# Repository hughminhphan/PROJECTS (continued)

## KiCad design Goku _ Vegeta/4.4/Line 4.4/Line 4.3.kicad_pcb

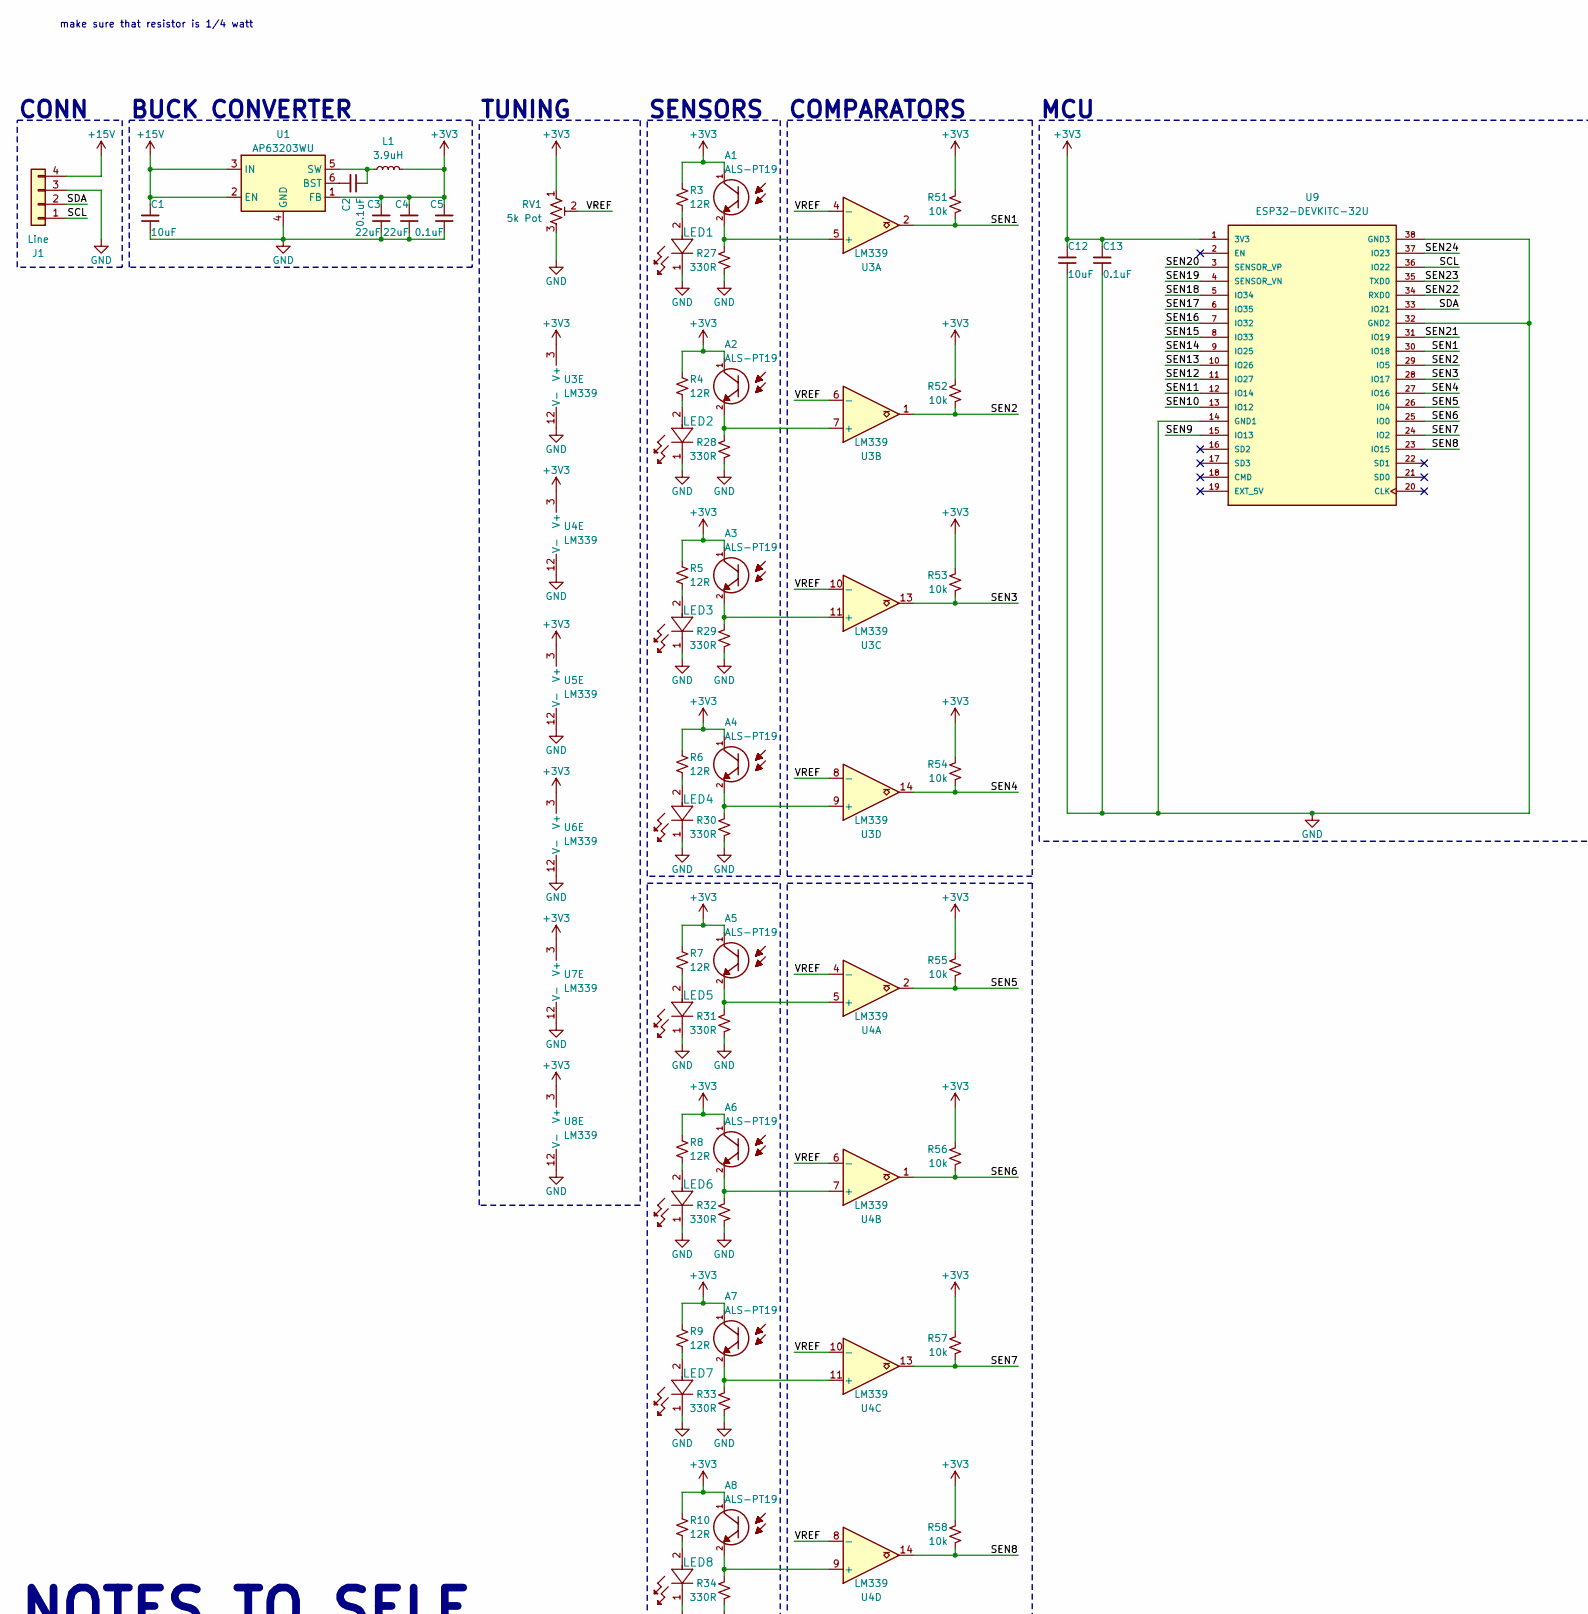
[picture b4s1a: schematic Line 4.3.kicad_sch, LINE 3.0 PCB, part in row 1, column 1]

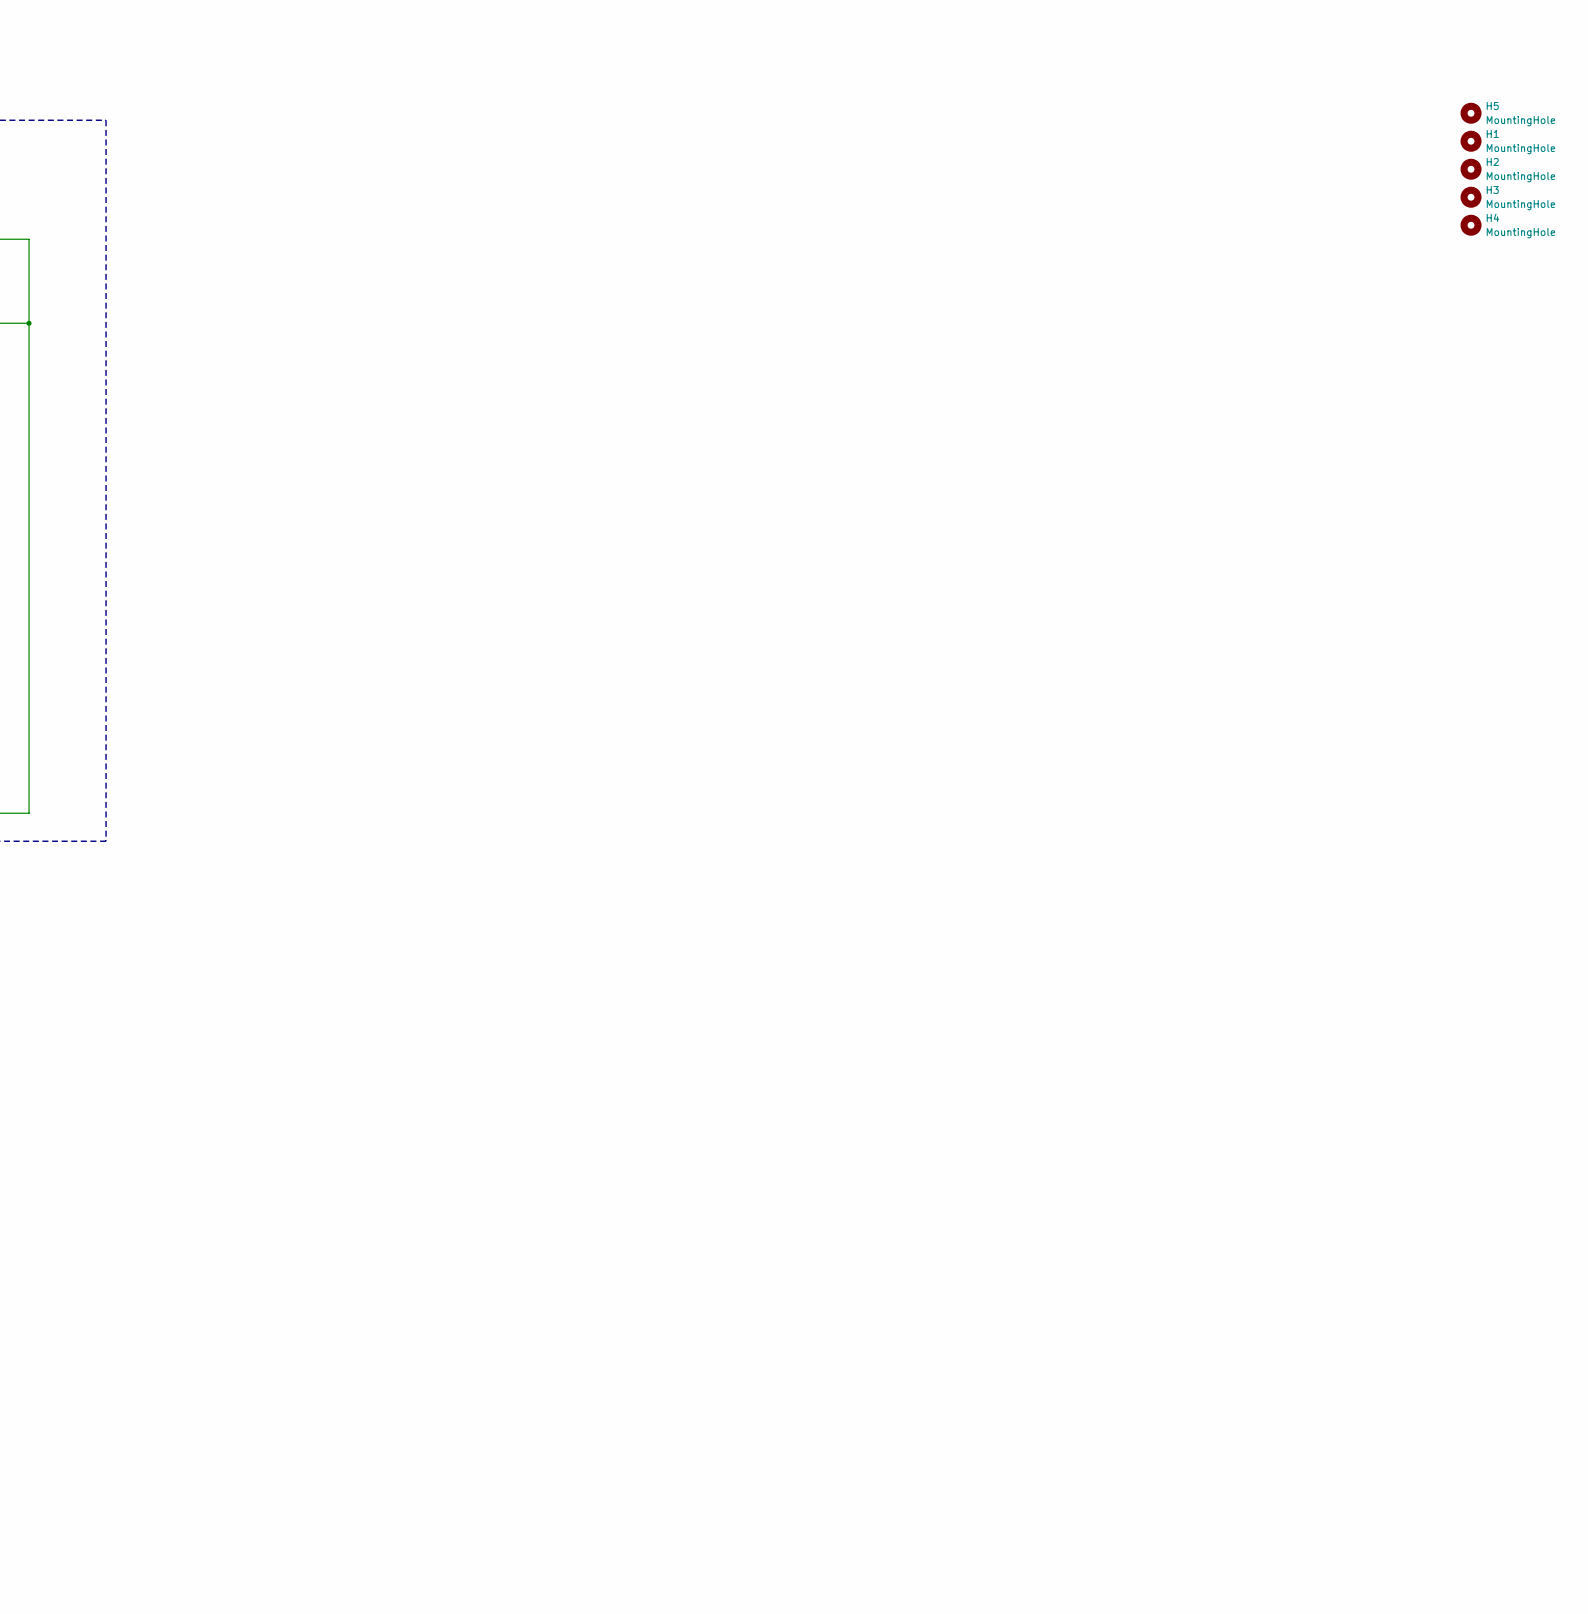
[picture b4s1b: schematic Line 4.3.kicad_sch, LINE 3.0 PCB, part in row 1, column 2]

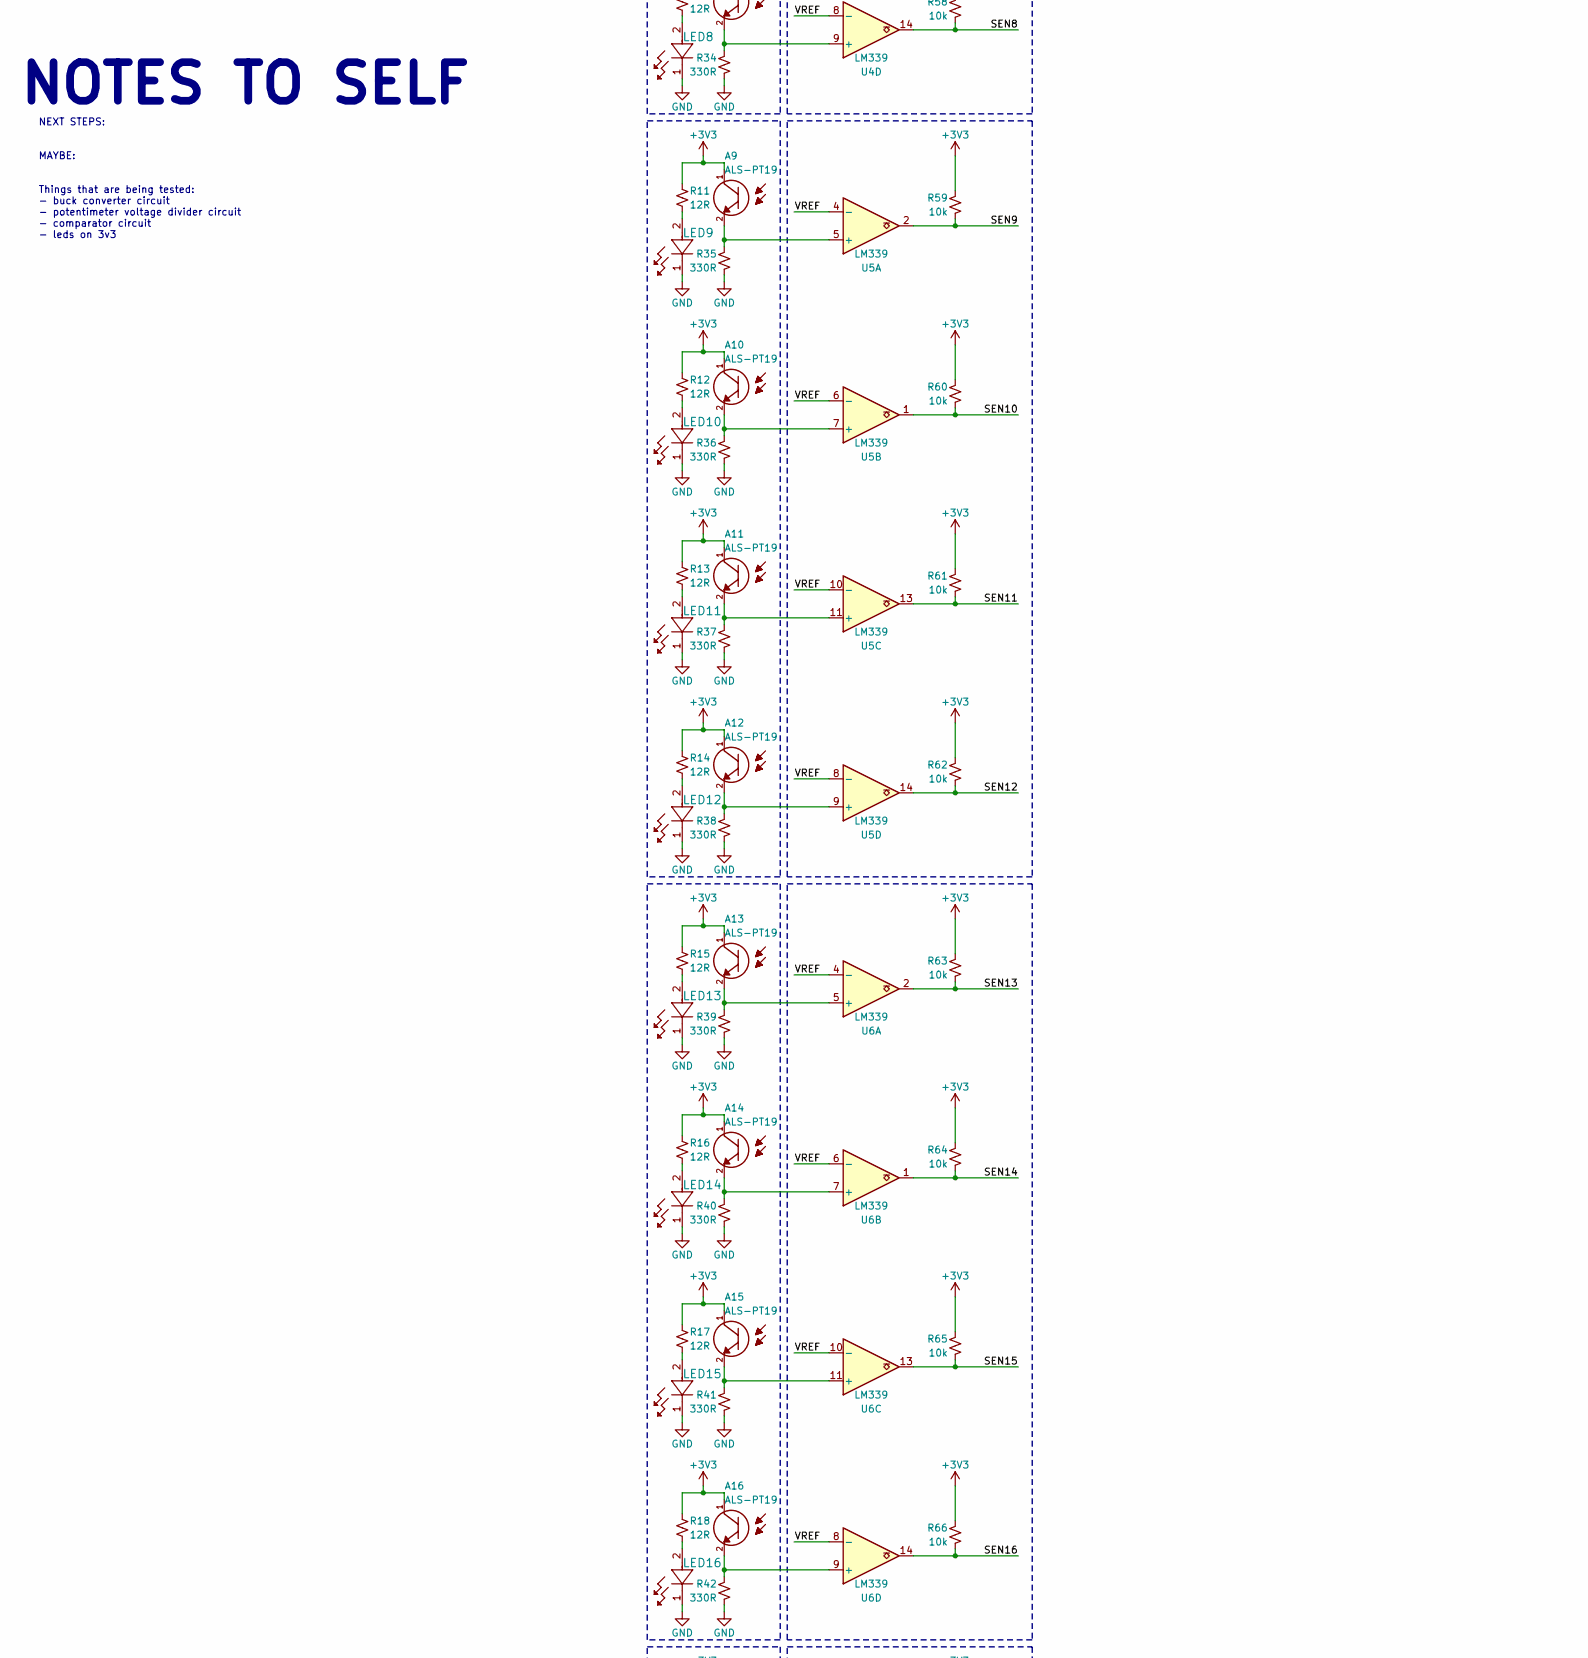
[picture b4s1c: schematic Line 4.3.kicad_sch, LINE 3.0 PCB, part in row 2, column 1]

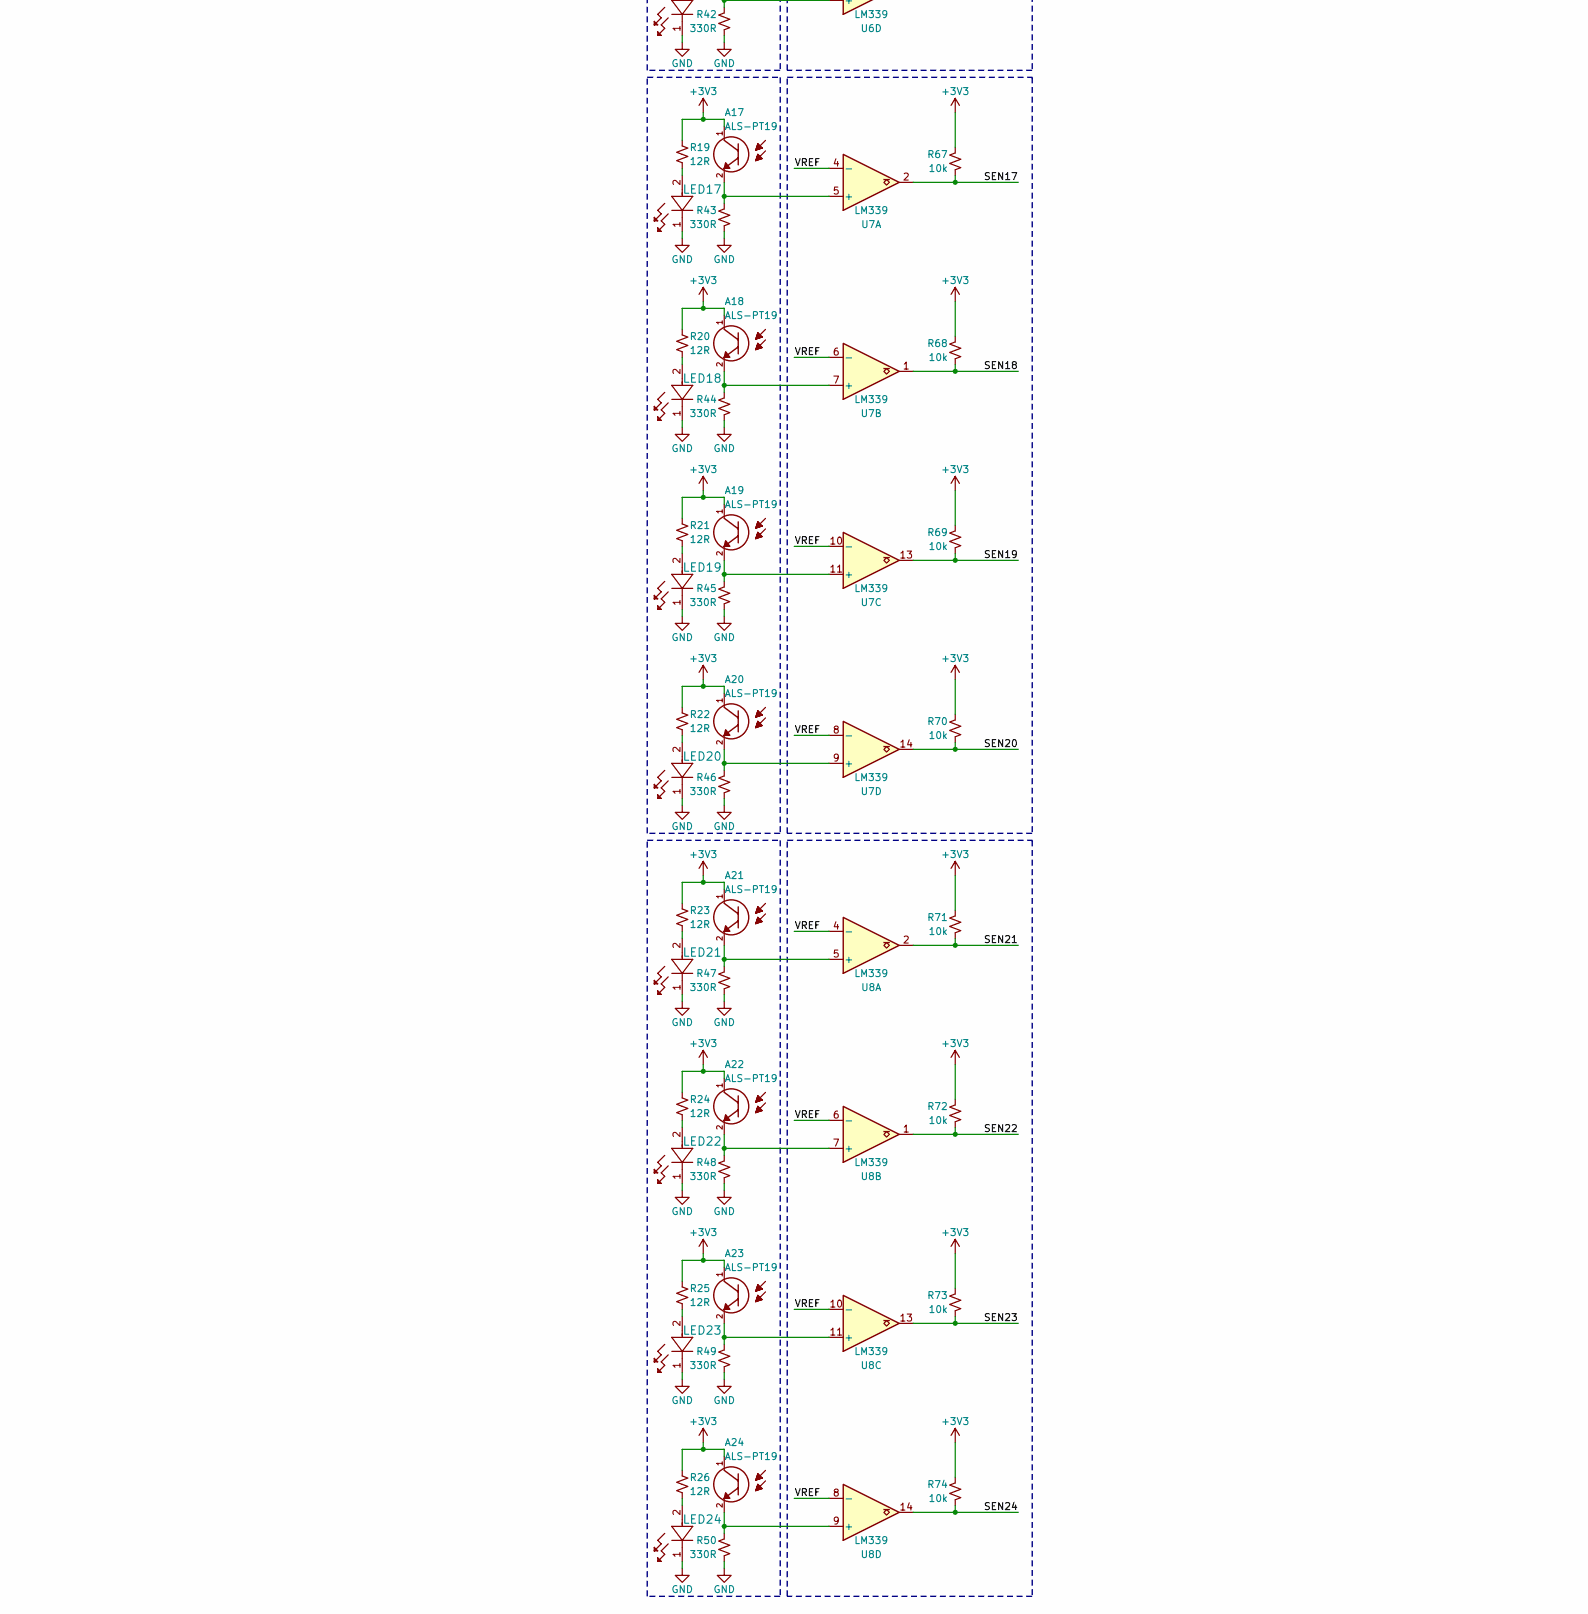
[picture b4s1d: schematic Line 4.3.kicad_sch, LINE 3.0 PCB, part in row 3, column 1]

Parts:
A1, A2, A3, A4, A5, A6, A7, A8, A9, A10, A11, A12, A13, A14, A15, A16, A17, A18, A19, A20, A21, A22, A23, A24: ALS-PT19; XDCR_ALS-PT19-315C_L177_TR8; PARTREV 5
C1, C12: 10uF; C_0805_2012Metric
C2, C5, C13: 0.1uF; C_0805_2012Metric
C3, C4: 22uF; C_0805_2012Metric
H1, H5: MountingHole; MountingHole_2.2mm_M2
H2, H3, H4: MountingHole; MountingHole_3.2mm_M3
J1: Line; JST_XH_B4B-XH-A_1x04_P2.50mm_Vertical
L1: 3.9uH; L_Bourns-SRU8043
LED1, LED2, LED3, LED4, LED5, LED6, LED7, LED8, LED9, LED10, LED11, LED12, LED13, LED14, LED15, LED16, LED17, LED18, LED19, LED20, LED21, LED22, LED23, LED24: JB2835AWT-W-U30GA0000-N0000001; LED_J2835_CRW
R3, R4, R5, R6, R7, R8, R9, R10, R11, R12, R13, R14, R15, R16, R17, R18, R19, R20, R21, R22, R23, R24, R25, R26: 12R; R_0805_2012Metric
R27, R28, R29, R30, R31, R32, R33, R34, R35, R36, R37, R38, R39, R40, R41, R42, R43, R44, R45, R46, R47, R48, R49, R50: 330R; R_0805_2012Metric
R51, R52, R53, R54, R55, R56, R57, R58, R59, R60, R61, R62, R63, R64, R65, R66, R67, R68, R69, R70, R71, R72, R73, R74: 10k; R_0805_2012Metric
RV1: 5k Pot; Potentiometer_Piher_PT-10-V10_Vertical
U1: AP63203WU; TSOT-23-6
U3, U4, U5, U6, U7, U8: LM339; TSSOP-14_W4.4mm
U9: ESP32-DEVKITC-32U; MODULE_ESP32-DEVKITC-32U; PARTREV N/A

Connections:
+3V3: A1.1, A2.1, A3.1, A4.1, A5.1, A6.1, A7.1, A8.1, A9.1, A10.1, A11.1, A12.1, A13.1, A14.1, A15.1, A16.1, A17.1, A18.1, A19.1, A20.1, A21.1, A22.1, A23.1, A24.1, C3.2, C4.2, C5.2, C12.2, C13.2, L1.2, R3.1, R4.1, R5.1, R6.1, R7.1, R8.1, R9.1, R10.1, R11.1, R12.1, R13.1, R14.1, R15.1, R16.1, R17.1, R18.1, R19.1, R20.1, R21.1, R22.1, R23.1, R24.1, R25.1, R26.1, R51.2, R52.2, R53.2, R54.2, R55.2, R56.2, R57.2, R58.2, R59.2, R60.2, R61.2, R62.2, R63.2, R64.2, R65.2, R66.2, R67.2, R68.2, R69.2, R70.2, R71.2, R72.2, R73.2, R74.2, RV1.1, U1.1 (FB), U3.3 (V+), U4.3 (V+), U5.3 (V+), U6.3 (V+), U7.3 (V+), U8.3 (V+), U9.1 (3V3)
+15V: C1.2, J1.4, U1.2 (EN), U1.3 (IN)
/SCL: J1.1, U9.36 (IO22)
/SDA: J1.2, U9.33 (IO21)
/SEN1: R51.1, U3.2, U9.30 (IO18)
/SEN2: R52.1, U3.1, U9.29 (IO5)
/SEN3: R53.1, U3.13, U9.28 (IO17)
/SEN4: R54.1, U3.14, U9.27 (IO16)
/SEN5: R55.1, U4.2, U9.26 (IO4)
/SEN6: R56.1, U4.1, U9.25 (IO0)
/SEN7: R57.1, U4.13, U9.24 (IO2)
/SEN8: R58.1, U4.14, U9.23 (IO15)
/SEN9: R59.1, U5.2, U9.15 (IO13)
/SEN10: R60.1, U5.1, U9.13 (IO12)
/SEN11: R61.1, U5.13, U9.12 (IO14)
/SEN12: R62.1, U5.14, U9.11 (IO27)
/SEN13: R63.1, U6.2, U9.10 (IO26)
/SEN14: R64.1, U6.1, U9.9 (IO25)
/SEN15: R65.1, U6.13, U9.8 (IO33)
/SEN16: R66.1, U6.14, U9.7 (IO32)
/SEN17: R67.1, U7.2, U9.6 (IO35)
/SEN18: R68.1, U7.1, U9.5 (IO34)
/SEN19: R69.1, U7.13, U9.4 (SENSOR_VN)
/SEN20: R70.1, U7.14, U9.3 (SENSOR_VP)
/SEN21: R71.1, U8.2, U9.31 (IO19)
/SEN22: R72.1, U8.1, U9.34 (RXD0)
/SEN23: R73.1, U8.13, U9.35 (TXD0)
/SEN24: R74.1, U8.14, U9.37 (IO23)
/VREF: RV1.2, U3.4 (-), U3.6 (-), U3.8 (-), U3.10 (-), U4.4 (-), U4.6 (-), U4.8 (-), U4.10 (-), U5.4 (-), U5.6 (-), U5.8 (-), U5.10 (-), U6.4 (-), U6.6 (-), U6.8 (-), U6.10 (-), U7.4 (-), U7.6 (-), U7.8 (-), U7.10 (-), U8.4 (-), U8.6 (-), U8.8 (-), U8.10 (-)
GND: C1.1, C3.1, C4.1, C5.1, C12.1, C13.1, J1.3, LED1.1, LED2.1, LED3.1, LED4.1, LED5.1, LED6.1, LED7.1, LED8.1, LED9.1, LED10.1, LED11.1, LED12.1, LED13.1, LED14.1, LED15.1, LED16.1, LED17.1, LED18.1, LED19.1, LED20.1, LED21.1, LED22.1, LED23.1, LED24.1, R27.1, R28.1, R29.1, R30.1, R31.1, R32.1, R33.1, R34.1, R35.1, R36.1, R37.1, R38.1, R39.1, R40.1, R41.1, R42.1, R43.1, R44.1, R45.1, R46.1, R47.1, R48.1, R49.1, R50.1, RV1.3, U1.4 (GND), U3.12 (V-), U4.12 (V-), U5.12 (V-), U6.12 (V-), U7.12 (V-), U8.12 (V-), U9.14 (GND1), U9.32 (GND2), U9.38 (GND3)
unnamed: LED1.2, R3.2
unnamed: LED2.2, R4.2
unnamed: LED3.2, R5.2
unnamed: LED4.2, R6.2
unnamed: LED5.2, R7.2
unnamed: LED6.2, R8.2
unnamed: LED7.2, R9.2
unnamed: LED8.2, R10.2
unnamed: LED9.2, R11.2
unnamed: LED10.2, R12.2
unnamed: LED11.2, R13.2
unnamed: LED12.2, R14.2
unnamed: LED13.2, R15.2
unnamed: LED14.2, R16.2
unnamed: LED15.2, R17.2
unnamed: LED16.2, R18.2
unnamed: LED17.2, R19.2
unnamed: LED18.2, R20.2
unnamed: LED19.2, R21.2
unnamed: LED20.2, R22.2
unnamed: LED21.2, R23.2
unnamed: LED22.2, R24.2
unnamed: LED23.2, R25.2
unnamed: LED24.2, R26.2
unnamed: C2.2, U1.6 (BST)
unnamed: C2.1, L1.1, U1.5 (SW)
unnamed: A1.2, R27.2, U3.5 (+)
unnamed: A2.2, R28.2, U3.7 (+)
unnamed: A3.2, R29.2, U3.11 (+)
unnamed: A4.2, R30.2, U3.9 (+)
unnamed: A5.2, R31.2, U4.5 (+)
unnamed: A6.2, R32.2, U4.7 (+)
unnamed: A7.2, R33.2, U4.11 (+)
unnamed: A8.2, R34.2, U4.9 (+)
unnamed: A9.2, R35.2, U5.5 (+)
unnamed: A10.2, R36.2, U5.7 (+)
unnamed: A11.2, R37.2, U5.11 (+)
unnamed: A12.2, R38.2, U5.9 (+)
unnamed: A13.2, R39.2, U6.5 (+)
unnamed: A14.2, R40.2, U6.7 (+)
unnamed: A15.2, R41.2, U6.11 (+)
unnamed: A16.2, R42.2, U6.9 (+)
unnamed: A17.2, R43.2, U7.5 (+)
unnamed: A18.2, R44.2, U7.7 (+)
unnamed: A19.2, R45.2, U7.11 (+)
unnamed: A20.2, R46.2, U7.9 (+)
unnamed: A21.2, R47.2, U8.5 (+)
unnamed: A22.2, R48.2, U8.7 (+)
unnamed: A23.2, R49.2, U8.11 (+)
unnamed: A24.2, R50.2, U8.9 (+)

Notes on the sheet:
NOTES TO SELF
NEXT STEPS: MAYBE: Things that are being tested: - buck converter circuit - potentimeter voltage divider circuit - comparator circuit - leds on 3v3
SENSORS
TUNING
make sure that resistor is 1/4 watt
CONN
MCU
BUCK CONVERTER
COMPARATORS

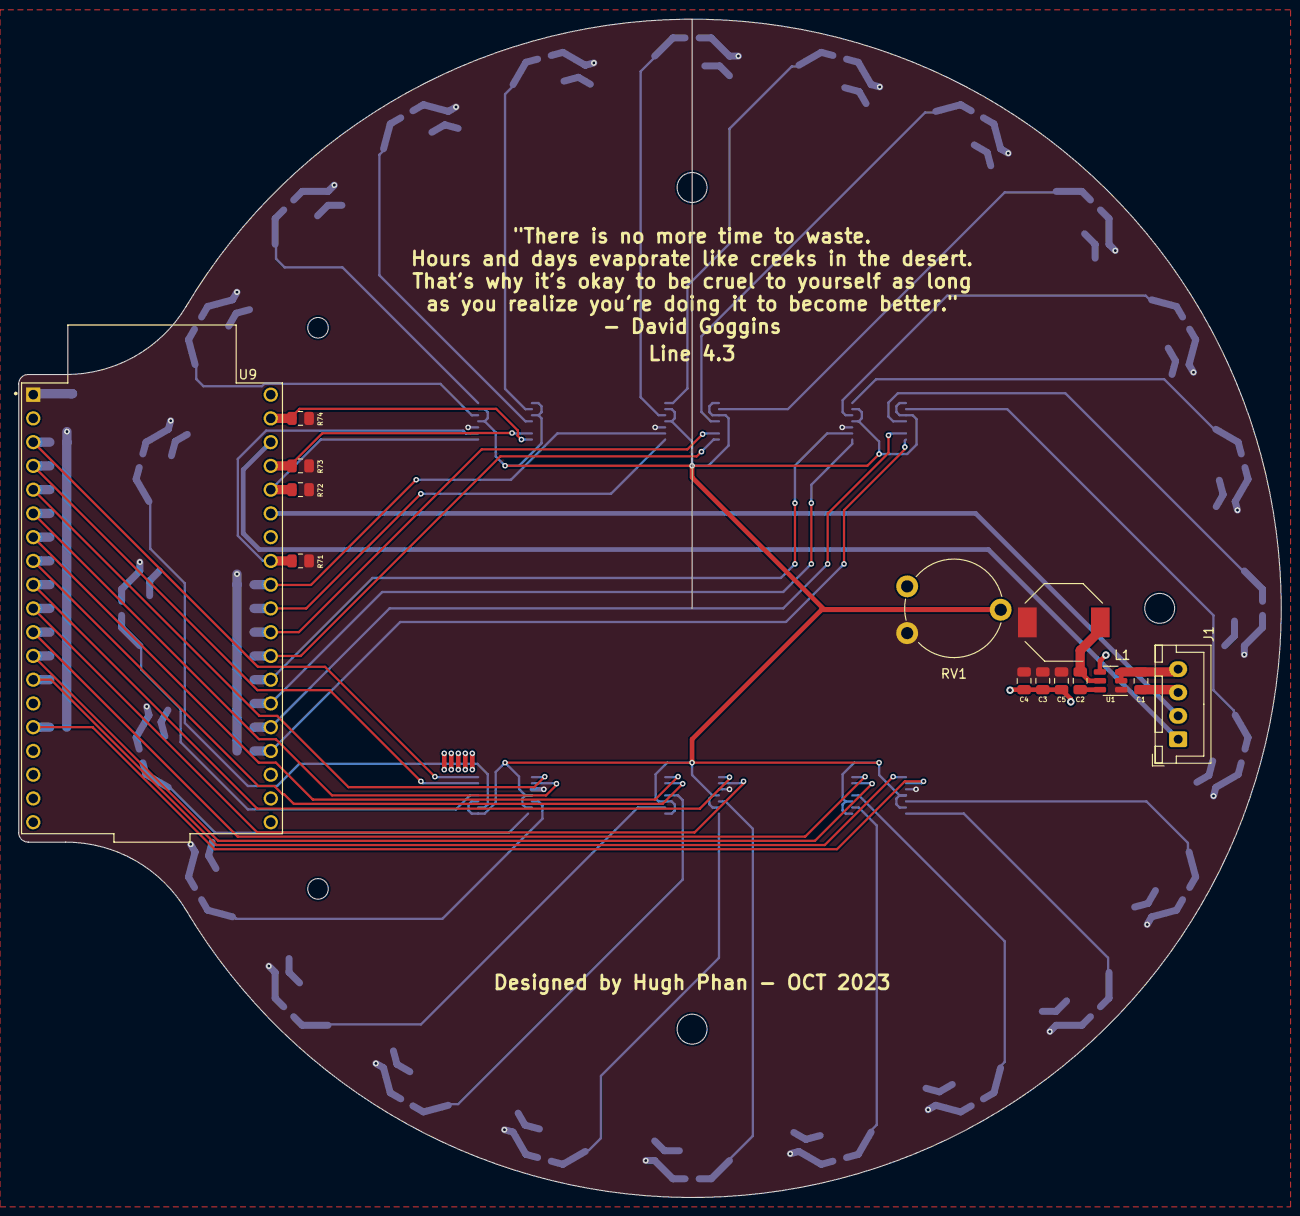
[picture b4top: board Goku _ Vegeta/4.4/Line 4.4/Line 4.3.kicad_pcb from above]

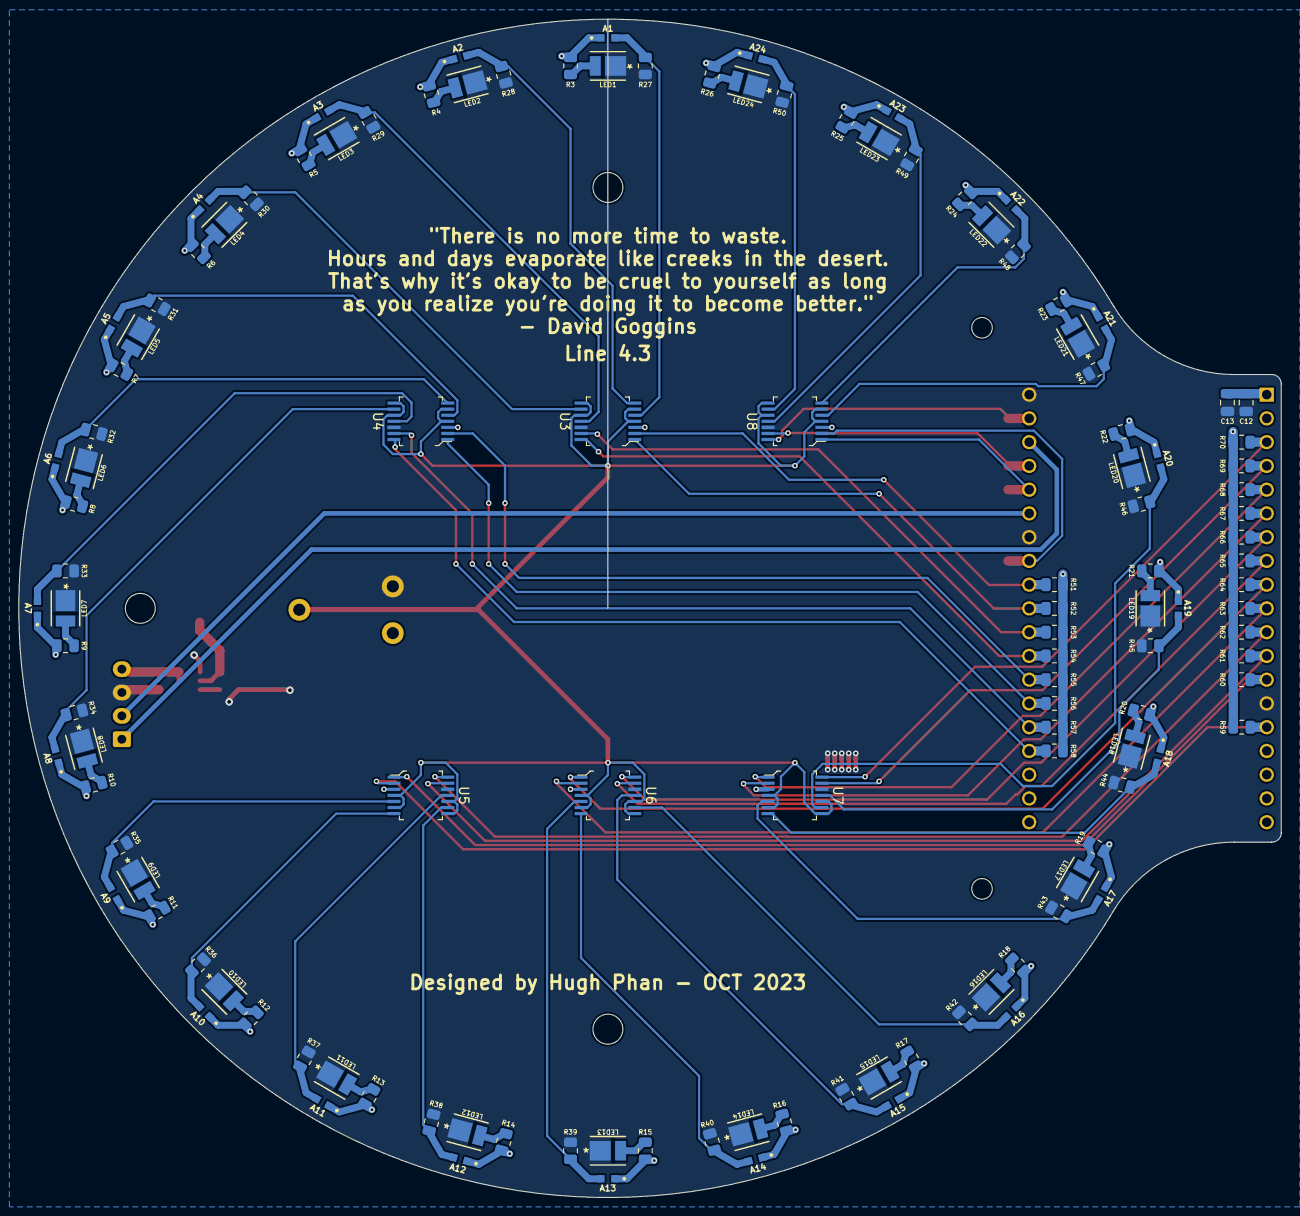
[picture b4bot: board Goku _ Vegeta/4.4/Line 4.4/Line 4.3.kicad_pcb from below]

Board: 2 copper layers, 135.0 x 126.0 mm, 143 parts (124 on the bottom side), 80 nets.
